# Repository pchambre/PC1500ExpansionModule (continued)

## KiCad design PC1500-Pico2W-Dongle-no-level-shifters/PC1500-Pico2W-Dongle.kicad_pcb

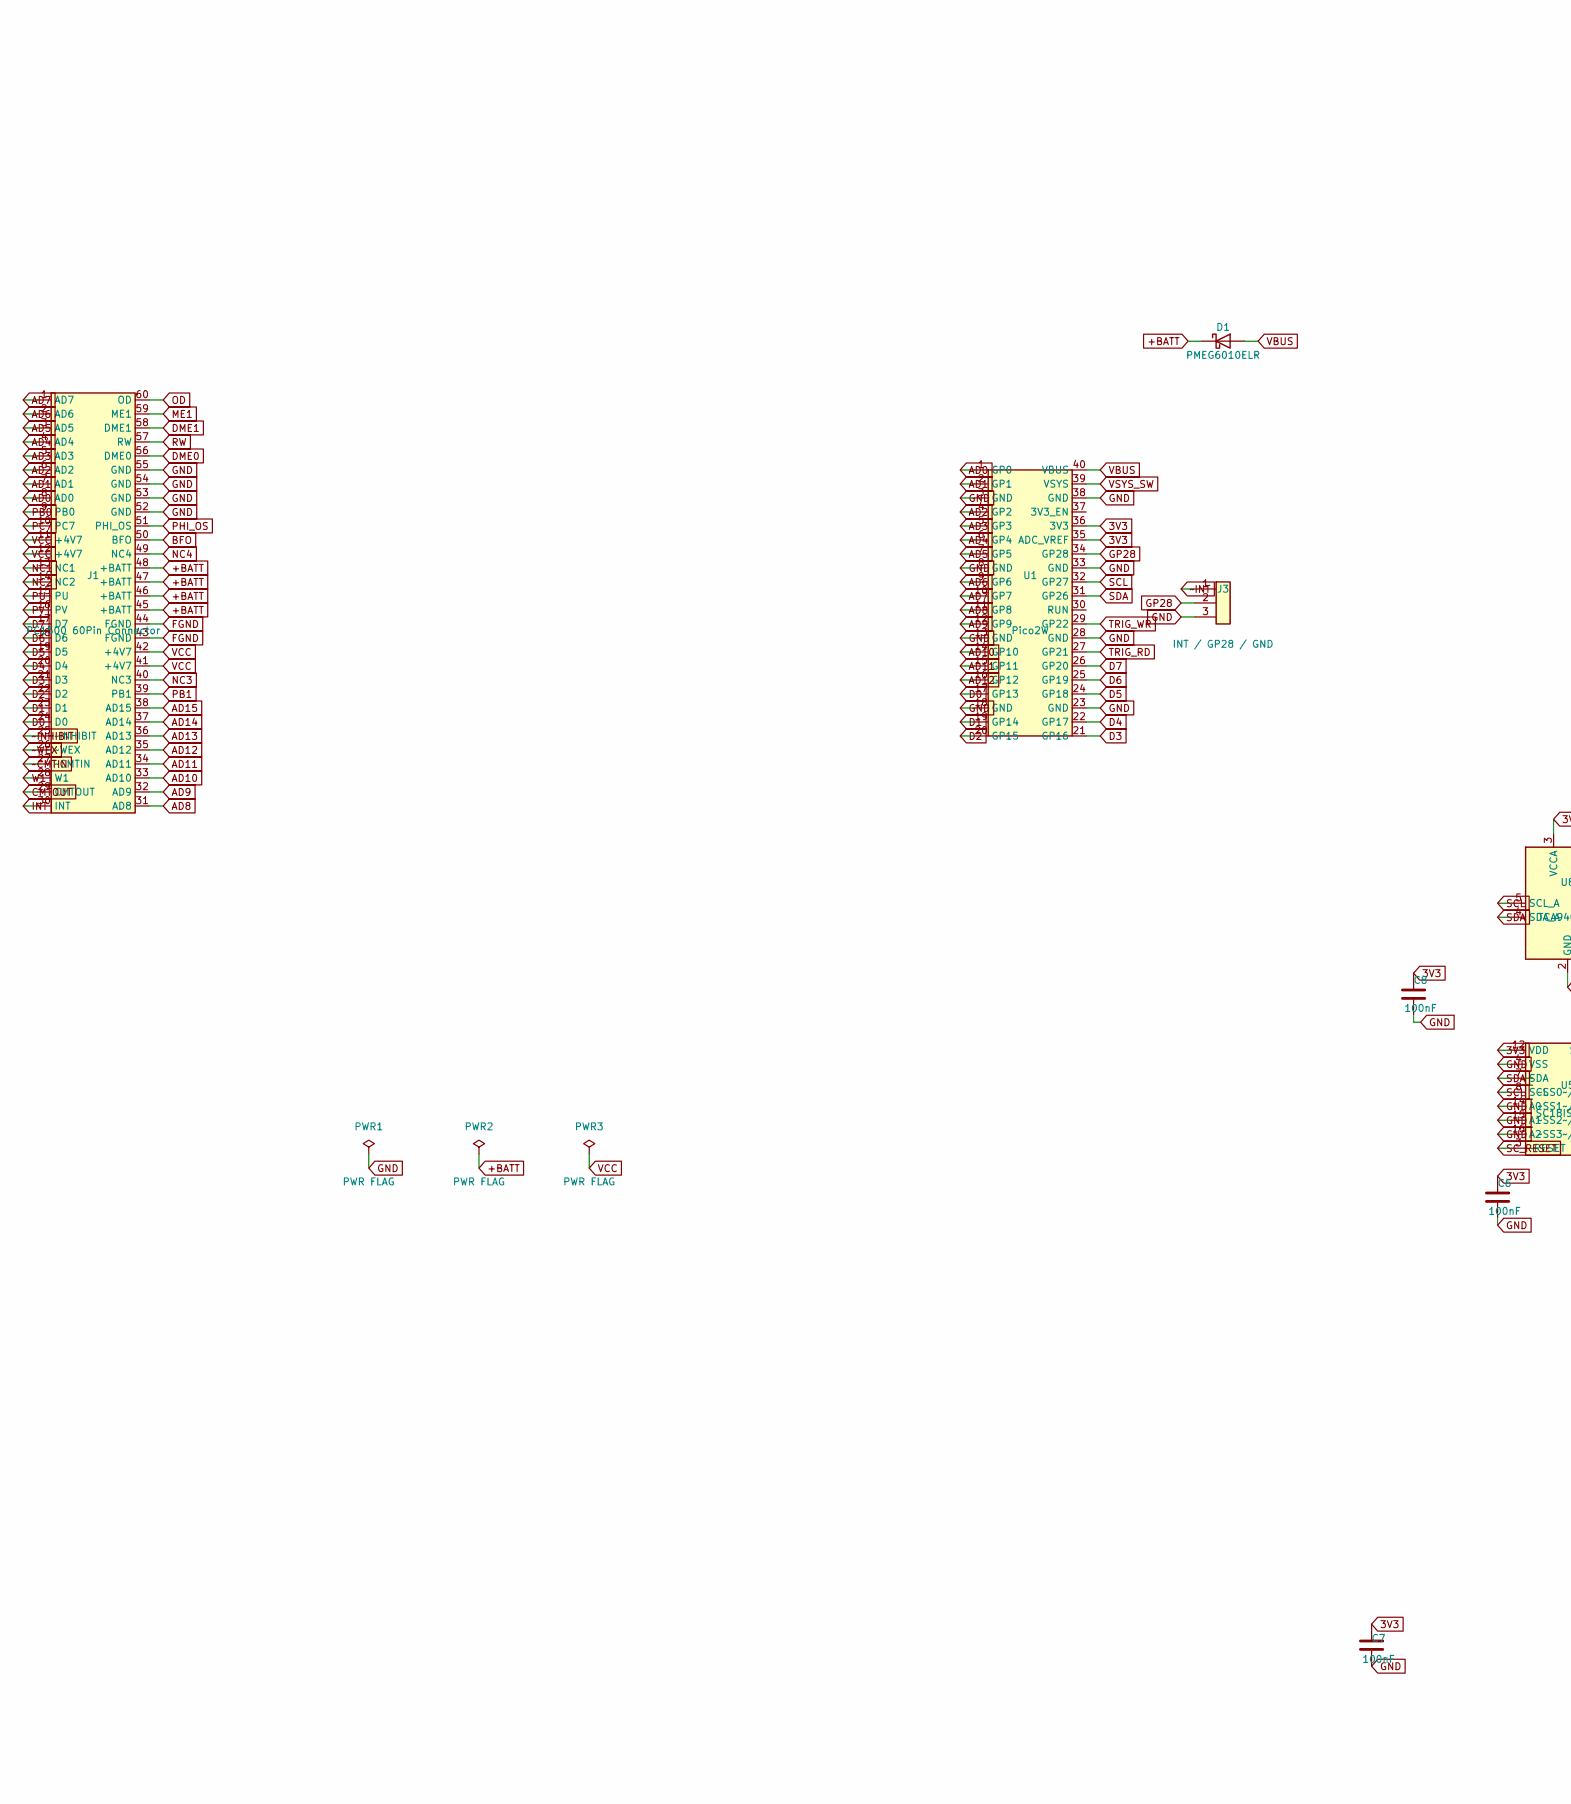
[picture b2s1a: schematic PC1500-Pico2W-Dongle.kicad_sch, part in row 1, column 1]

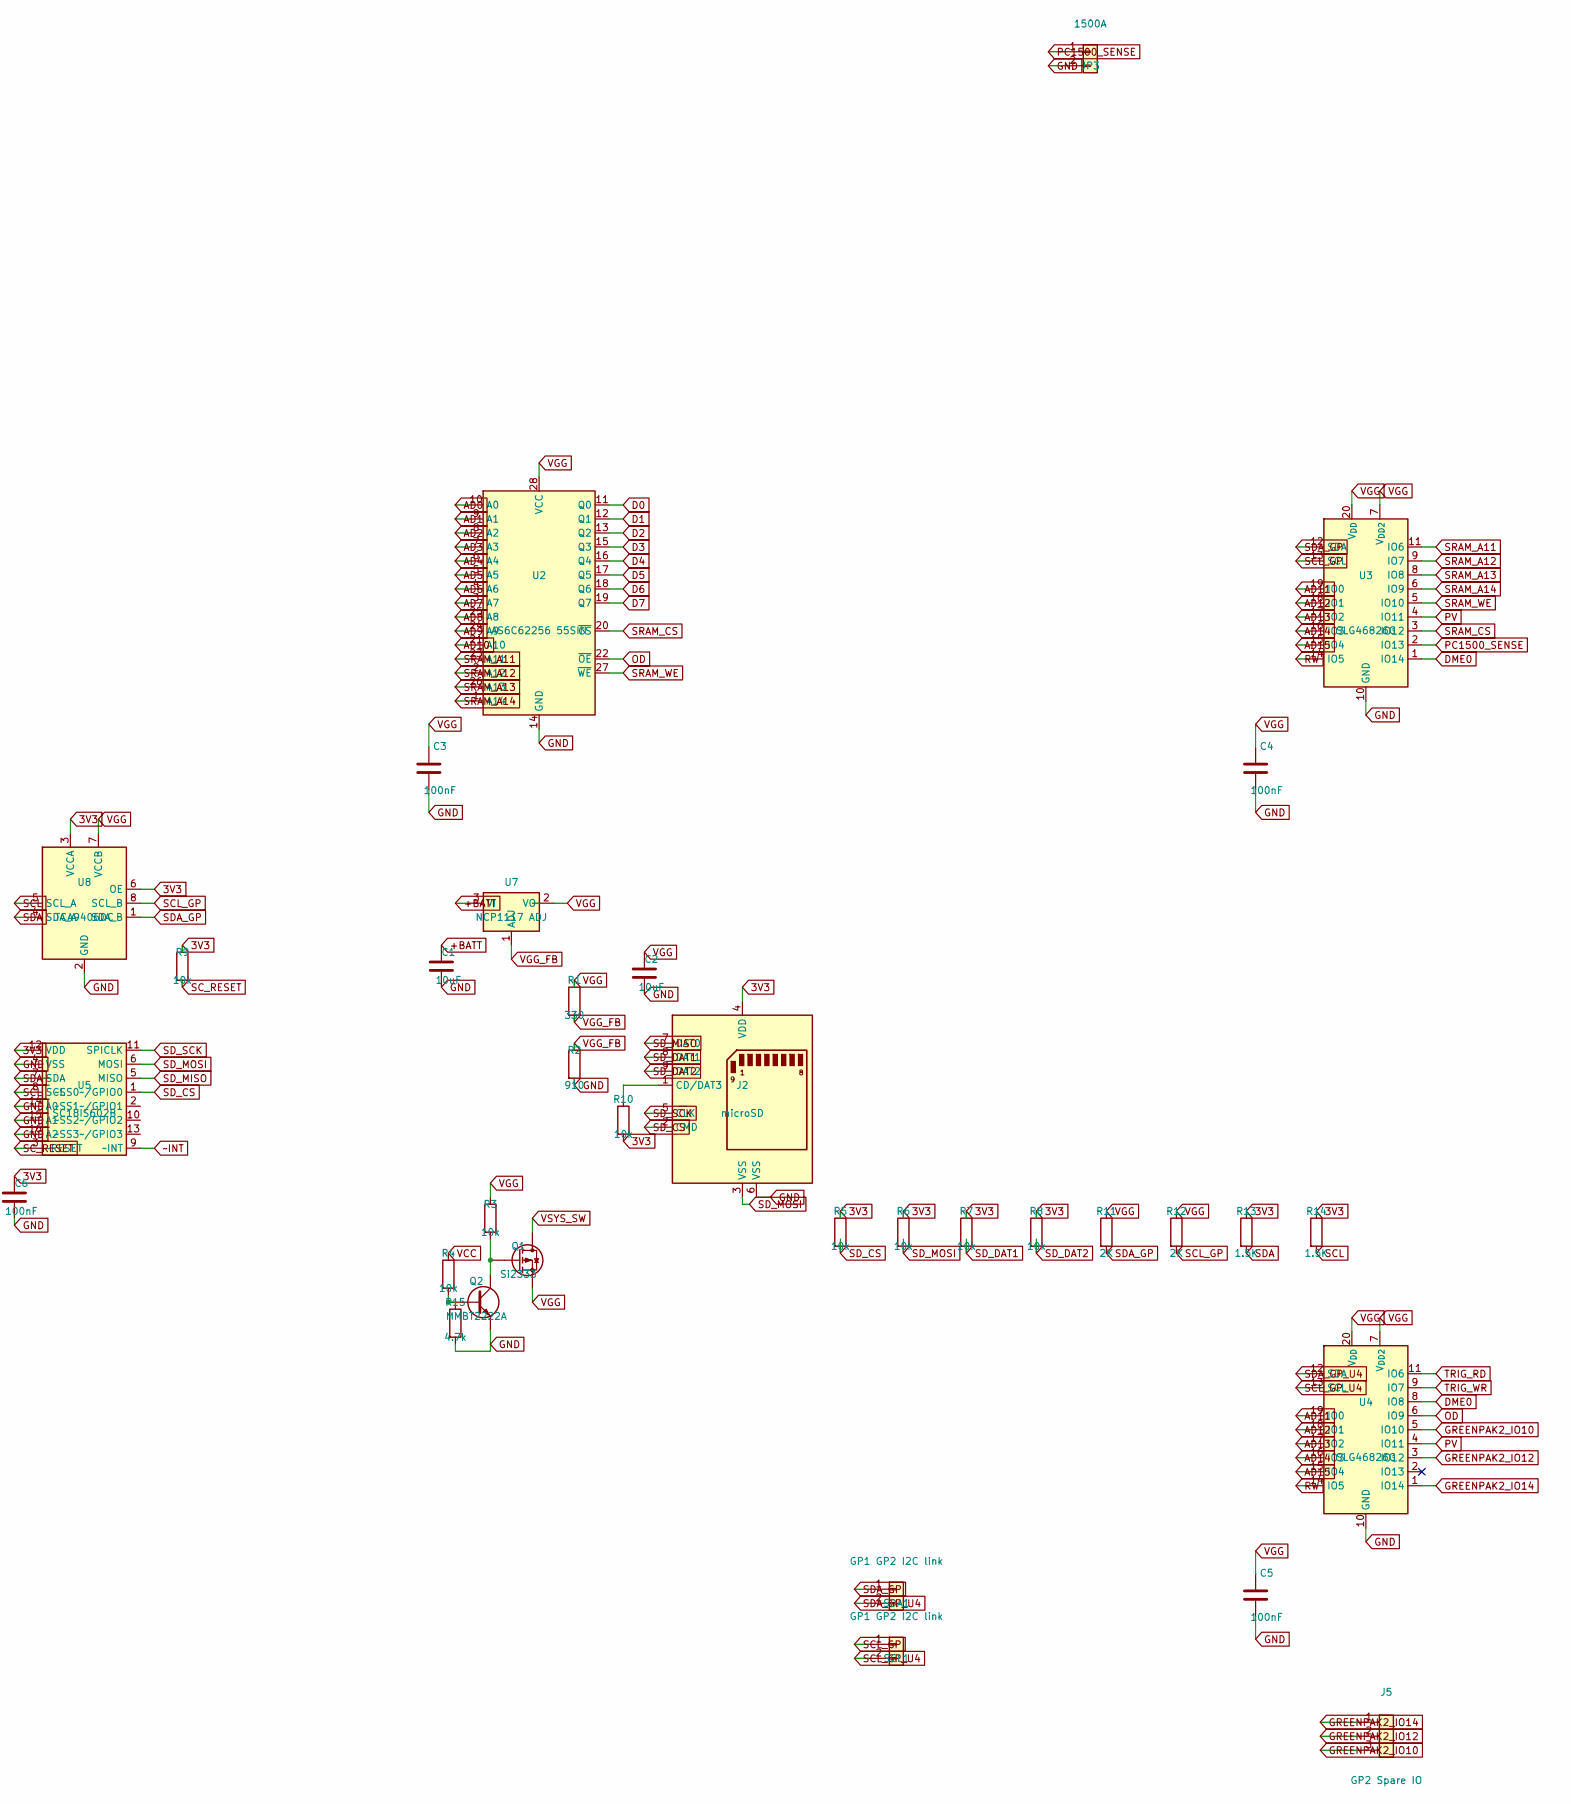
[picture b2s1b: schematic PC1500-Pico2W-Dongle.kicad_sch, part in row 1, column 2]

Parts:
C1, C2: 10uF; C_0603_1608Metric
C3, C4, C5, C6, C7, C8: 100nF; C_0603_1608Metric
D1: PMEG6010ELR; D_SOD-123F
J1: PC1500 60Pin Connector; HIF6A-60PA-1.27DS
J2: microSD; microSD_HC_Molex_104031-0811
J3: INT / GP28 / GND; PinHeader_1x03_P2.54mm_Vertical
J5: GP2 Spare IO; PinHeader_1x03_P2.54mm_Vertical
JP3: 1500A; PinHeader_1x02_P2.54mm_Vertical
PWR1, PWR2, PWR3: PWR FLAG
Q1: Si2333; SOT-23
Q2: MMBT2222A; SOT-23
R1: 330; R_0603_1608Metric
R2: 910; R_0603_1608Metric
R3, R4, R5, R6, R7, R8, R9, R10: 10k; R_0201_0603Metric
R11, R12: 2K; R_0201_0603Metric
R13, R14: 1.5K; R_0201_0603Metric
R15: 4.7k; R_0201_0603Metric
SCL1: GP1 GP2 I2C link; PinHeader_1x02_P2.54mm_Vertical
SDA1: GP1 GP2 I2C link; PinHeader_1x02_P2.54mm_Vertical
U1: Pico2W; Pico2W-Socket
U2: AS6C62256 55SIN; SOP-28_8.4x18.16mm_P1.27mm
U3, U4: SLG46826G; TSSOP-20_4.4x6.5mm_P0.65mm
U5: SC18IS602B; TSSOP-16_4.4x5mm_P0.65mm
U7: NCP1117 ADJ; SOT-223-3_TabPin2
U8: TCA9406DC; VSSOP-8_3x3mm_P0.65mm

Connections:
3V3: C6.1, C7.1, C8.1, J2.4 (VDD), R5.1, R6.1, R7.1, R8.1, R9.1, R10.2, R13.1, R14.1, U1.35 (ADC_VREF), U1.36 (3V3), U5.12 (VDD), U8.3 (VCCA), U8.6 (OE)
+BATT: C1.1, D1.1 (K), J1.45 (+BATT), J1.46 (+BATT), J1.47 (+BATT), J1.48 (+BATT), PWR2.1, U7.3 (VI)
AD0: J1.8 (AD0), U1.1 (GP0), U2.10 (A0)
AD1: J1.7 (AD1), U1.2 (GP1), U2.9 (A1)
AD2: J1.6 (AD2), U1.4 (GP2), U2.8 (A2)
AD3: J1.5 (AD3), U1.5 (GP3), U2.7 (A3)
AD4: J1.4 (AD4), U1.6 (GP4), U2.6 (A4)
AD5: J1.3 (AD5), U1.7 (GP5), U2.5 (A5)
AD6: J1.2 (AD6), U1.9 (GP6), U2.4 (A6)
AD7: J1.1 (AD7), U1.10 (GP7), U2.3 (A7)
AD8: J1.31 (AD8), U1.11 (GP8), U2.25 (A8)
AD9: J1.32 (AD9), U1.12 (GP9), U2.24 (A9)
AD10: J1.33 (AD10), U1.14 (GP10), U2.21 (A10)
AD11: J1.34 (AD11), U1.15 (GP11), U3.19 (IO0), U4.19 (IO0)
AD12: J1.35 (AD12), U1.16 (GP12), U3.18 (IO1), U4.18 (IO1)
AD13: J1.36 (AD13), U3.17 (IO2), U4.17 (IO2)
AD14: J1.37 (AD14), U3.16 (IO3), U4.16 (IO3)
AD15: J1.38 (AD15), U3.15 (IO4), U4.15 (IO4)
BFO: J1.50 (BFO)
CMTOUT: J1.29 (CMTOUT)
D0: J1.24 (D0), U1.17 (GP13), U2.11 (Q0)
D1: J1.23 (D1), U1.19 (GP14), U2.12 (Q1)
D2: J1.22 (D2), U1.20 (GP15), U2.13 (Q2)
D3: J1.21 (D3), U1.21 (GP16), U2.15 (Q3)
D4: J1.20 (D4), U1.22 (GP17), U2.16 (Q4)
D5: J1.19 (D5), U1.24 (GP18), U2.17 (Q5)
D6: J1.18 (D6), U1.25 (GP19), U2.18 (Q6)
D7: J1.17 (D7), U1.26 (GP20), U2.19 (Q7)
DME0: J1.56 (DME0), U3.1 (IO14), U4.8 (IO8)
DME1: J1.58 (DME1)
FGND: J1.43 (FGND), J1.44 (FGND)
GND: C1.2, C2.2, C3.2, C4.2, C5.2, C6.2, C7.2, C8.2, J1.52 (GND), J1.53 (GND), J1.54 (GND), J1.55 (GND), J2.6 (VSS), J3.3, JP3.2, PWR1.1, Q2.2 (E), R2.2, R15.2, U1.3 (GND), U1.8 (GND), U1.13 (GND), U1.18 (GND), U1.23 (GND), U1.28 (GND), U1.33 (GND), U1.38 (GND), U2.14 (GND), U3.10 (GND), U4.10 (GND), U5.4 (VSS), U5.14 (A0), U5.15 (A1), U5.16 (A2), U8.2 (GND)
GP28: J3.2, U1.34 (GP28)
GREENPAK2_IO10: J5.3, U4.5 (IO10)
GREENPAK2_IO12: J5.2, U4.3 (IO12)
GREENPAK2_IO14: J5.1, U4.1 (IO14)
INT: J1.30 (INT)
ME1: J1.59 (ME1)
NC1: J1.13 (NC1)
NC2: J1.14 (NC2)
NC3: J1.40 (NC3)
NC4: J1.49 (NC4)
unnamed: J2.1 (CD/DAT3), R10.1
unnamed: Q1.1 (G), Q2.3 (C), R3.2
unnamed: Q2.1 (B), R4.2, R15.1
OD: J1.60 (OD), U2.22 (~OE), U4.6 (IO9)
PB0: J1.9 (PB0)
PB1: J1.39 (PB1)
PC7: J1.10 (PC7)
PC1500_SENSE: JP3.1, U3.2 (IO13)
PHI_OS: J1.51 (PHI_OS)
PU: J1.15 (PU)
PV: J1.16 (PV), U3.4 (IO11), U4.4 (IO11)
RW: J1.57 (RW), U3.14 (IO5), U4.14 (IO5)
SCL: R14.2, U1.32 (GP27), U5.8 (SCL), U8.5 (SCL_A)
SCL_GP: R12.2, SCL1.1, U3.13 (SCL), U8.8 (SCL_B)
SCL_GP_U4: SCL1.2, U4.13 (SCL)
SC_RESET: R9.2, U5.3 (~RESET)
SDA: R13.2, U1.31 (GP26), U5.7 (SDA), U8.4 (SDA_A)
SDA_GP: R11.2, SDA1.1, U3.12 (SDA), U8.1 (SDA_B)
SDA_GP_U4: SDA1.2, U4.12 (SDA)
SD_CS: J2.2 (CMD), R5.2, U5.1 (~SS0~/GPIO0)
SD_DAT1: J2.8 (DAT1), R7.2
SD_DAT2: J2.9 (DAT2), R8.2
SD_MISO: J2.7 (DAT0), U5.5 (MISO)
SD_MOSI: J2.3 (VSS), R6.2, U5.6 (MOSI)
SD_SCK: J2.5 (CLK), U5.11 (SPICLK)
SRAM_A11: U2.23 (A11), U3.11 (IO6)
SRAM_A12: U2.2 (A12), U3.9 (IO7)
SRAM_A13: U2.26 (A13), U3.8 (IO8)
SRAM_A14: U2.1 (A14), U3.6 (IO9)
SRAM_CS: U2.20 (~CS), U3.3 (IO12)
SRAM_WE: U2.27 (~WE), U3.5 (IO10)
TRIG_RD: U1.27 (GP21), U4.11 (IO6)
TRIG_WR: U1.29 (GP22), U4.9 (IO7)
VBUS: D1.2 (A), U1.40 (VBUS)
VCC: J1.11 (+4V7), J1.12 (+4V7), J1.41 (+4V7), J1.42 (+4V7), PWR3.1, R4.1
VGG: C2.1, C3.1, C4.1, C5.1, Q1.2 (S), R1.1, R3.1, R11.1, R12.1, U2.28 (VCC), U3.7 (V_{DD2}), U3.20 (V_{DD}), U4.7 (V_{DD2}), U4.20 (V_{DD}), U7.2 (VO), U8.7 (VCCB)
VGG_FB: R1.2, R2.1, U7.1 (ADJ)
VSYS_SW: Q1.3 (D), U1.39 (VSYS)
W1: J1.28 (W1)
~CMTIN: J1.27 (~CMTIN)
~INHIBIT: J1.25 (~INHIBIT)
~INT: J3.1, U5.9 (~INT)
~WEX: J1.26 (~WEX)

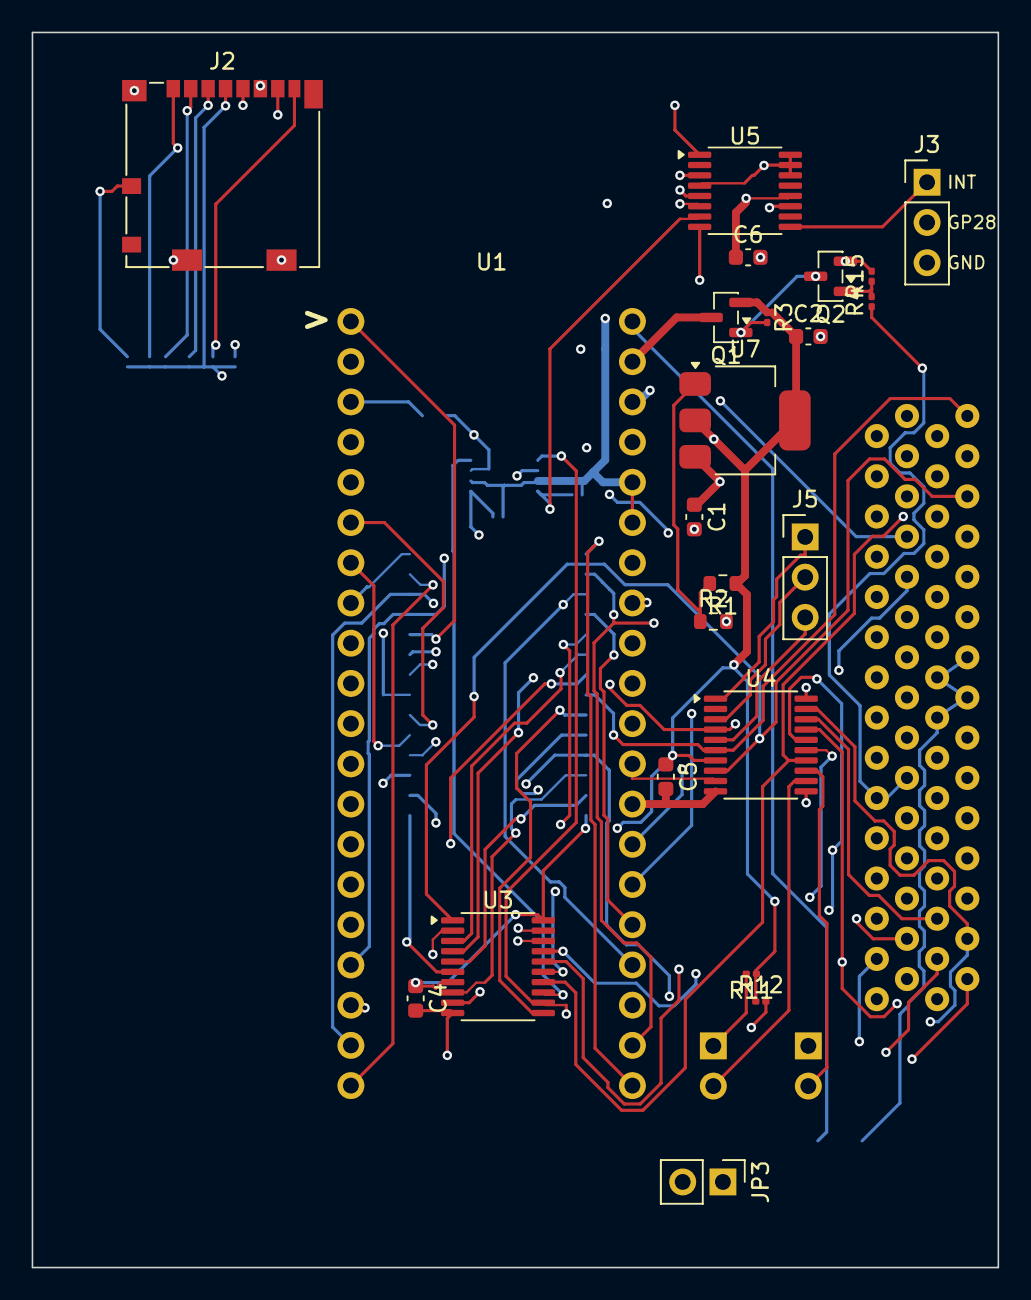
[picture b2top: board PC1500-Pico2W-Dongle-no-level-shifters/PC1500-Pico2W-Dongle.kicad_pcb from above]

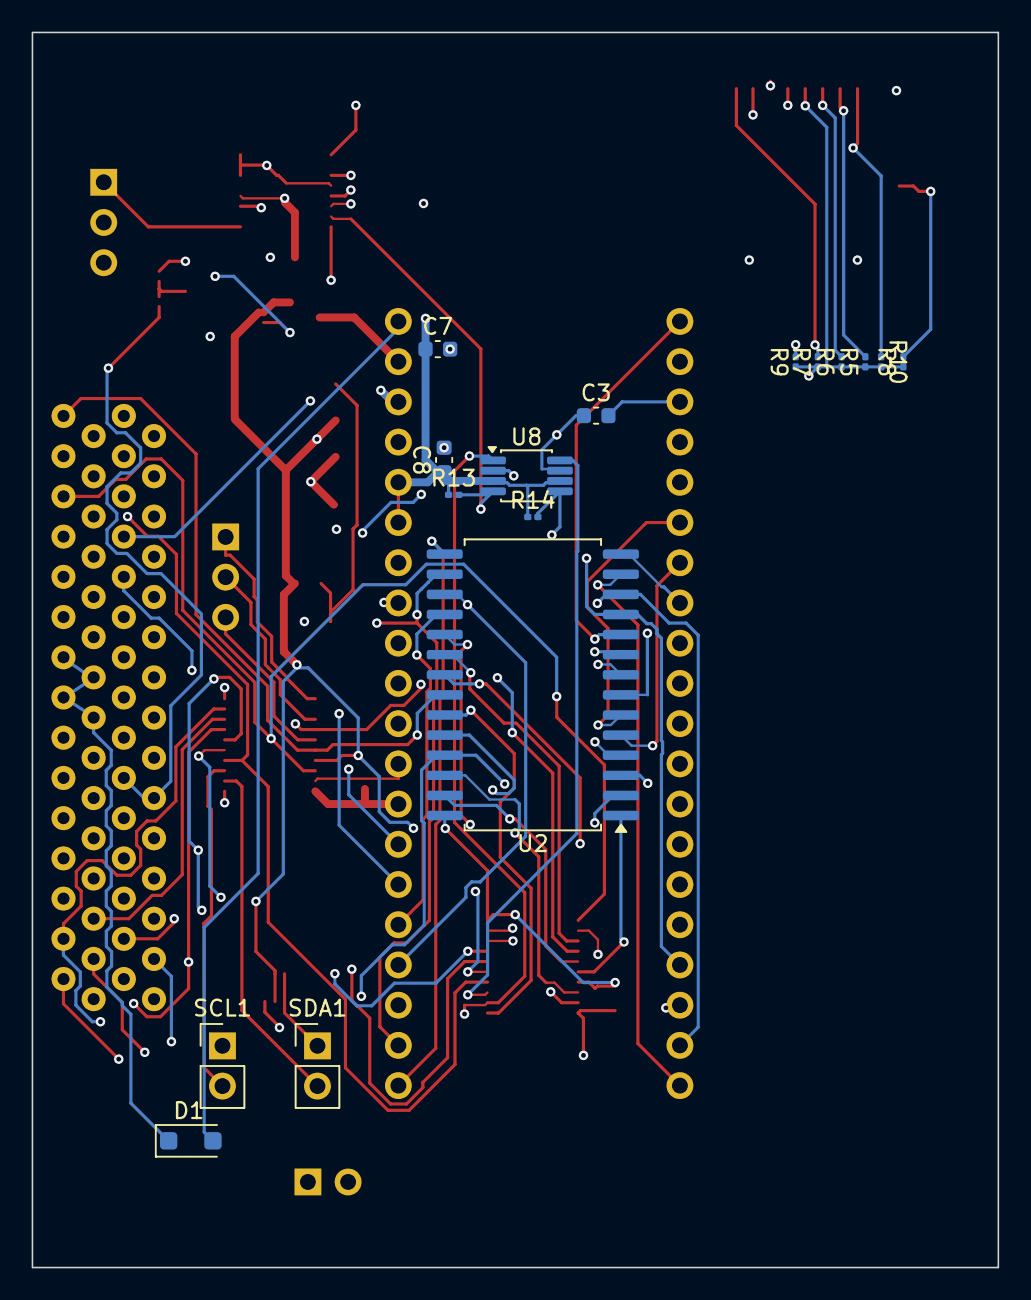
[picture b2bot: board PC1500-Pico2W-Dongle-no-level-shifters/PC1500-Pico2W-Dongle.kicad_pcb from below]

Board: 4 copper layers, 61.0 x 78.0 mm, 40 parts (16 on the bottom side), 67 nets.

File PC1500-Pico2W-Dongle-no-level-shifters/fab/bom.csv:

"Refs","Value","Footprint","Qty","DNP"
"C1,C2","10uF","Capacitor SMD:C 0603 1608Metric","2",""
"C3,C4,C5,C6,C7,C8","100nF","Capacitor SMD:C 0603 1608Metric","6",""
"D1","PMEG6010ELR","Diode SMD:D SOD 123F","1",""
"J1","PC1500 60Pin Connector","Pico2W Dongle Footprints:HIF6A 60PA 1.27DS","1",""
"J2","microSD","Connector Card:microSD HC Molex 104031 0811","1",""
"J3","INT / GP28 / GND","Connector PinHeader 2.54mm:PinHeader 1x03 P2.54mm Vertical","1",""
"J5","GP2 Spare IO","Connector PinHeader 2.54mm:PinHeader 1x03 P2.54mm Vertical","1",""
"JP3","1500A","Connector PinHeader 2.54mm:PinHeader 1x02 P2.54mm Vertical","1",""
"Q1","Si2333","Package TO SOT SMD:SOT 23","1",""
"Q2","MMBT2222A","Package TO SOT SMD:SOT 23","1",""
"R1","330Ω","Resistor SMD:R 0201 0603Metric","1",""
"R2","910Ω","Resistor SMD:R 0201 0603Metric","1",""
"R3,R4,R5,R6,R7,R8,R9,R10","10kΩ","Resistor SMD:R 0201 0603Metric","8",""
"R11,R12","2KΩ","Resistor SMD:R 0201 0603Metric","2",""
"R13,R14","1.5KΩ","Resistor SMD:R 0201 0603Metric","2",""
"SCL1,SDA1","GP1 GP2 I2C link","Connector PinHeader 2.54mm:PinHeader 1x02 P2.54mm Vertical","2",""
"U1","Pico2W","Pico2W Dongle Footprints:Pico2W Socket","1",""
"U2","AS6C62256 55SIN","Package SO:SOP 28 8.4x18.16mm P1.27mm","1",""
"U3,U4","SLG46826G","Package SO:TSSOP 20 4.4x6.5mm P0.65mm","2",""
"U5","SC18IS602B","Package SO:TSSOP 16 4.4x5mm P0.65mm","1",""
"U7","NCP1117 ADJ","Package TO SOT SMD:SOT 223 3 TabPin2","1",""
"U8","TCA9406DC","Package SO:VSSOP 8 3x3mm P0.65mm","1",""

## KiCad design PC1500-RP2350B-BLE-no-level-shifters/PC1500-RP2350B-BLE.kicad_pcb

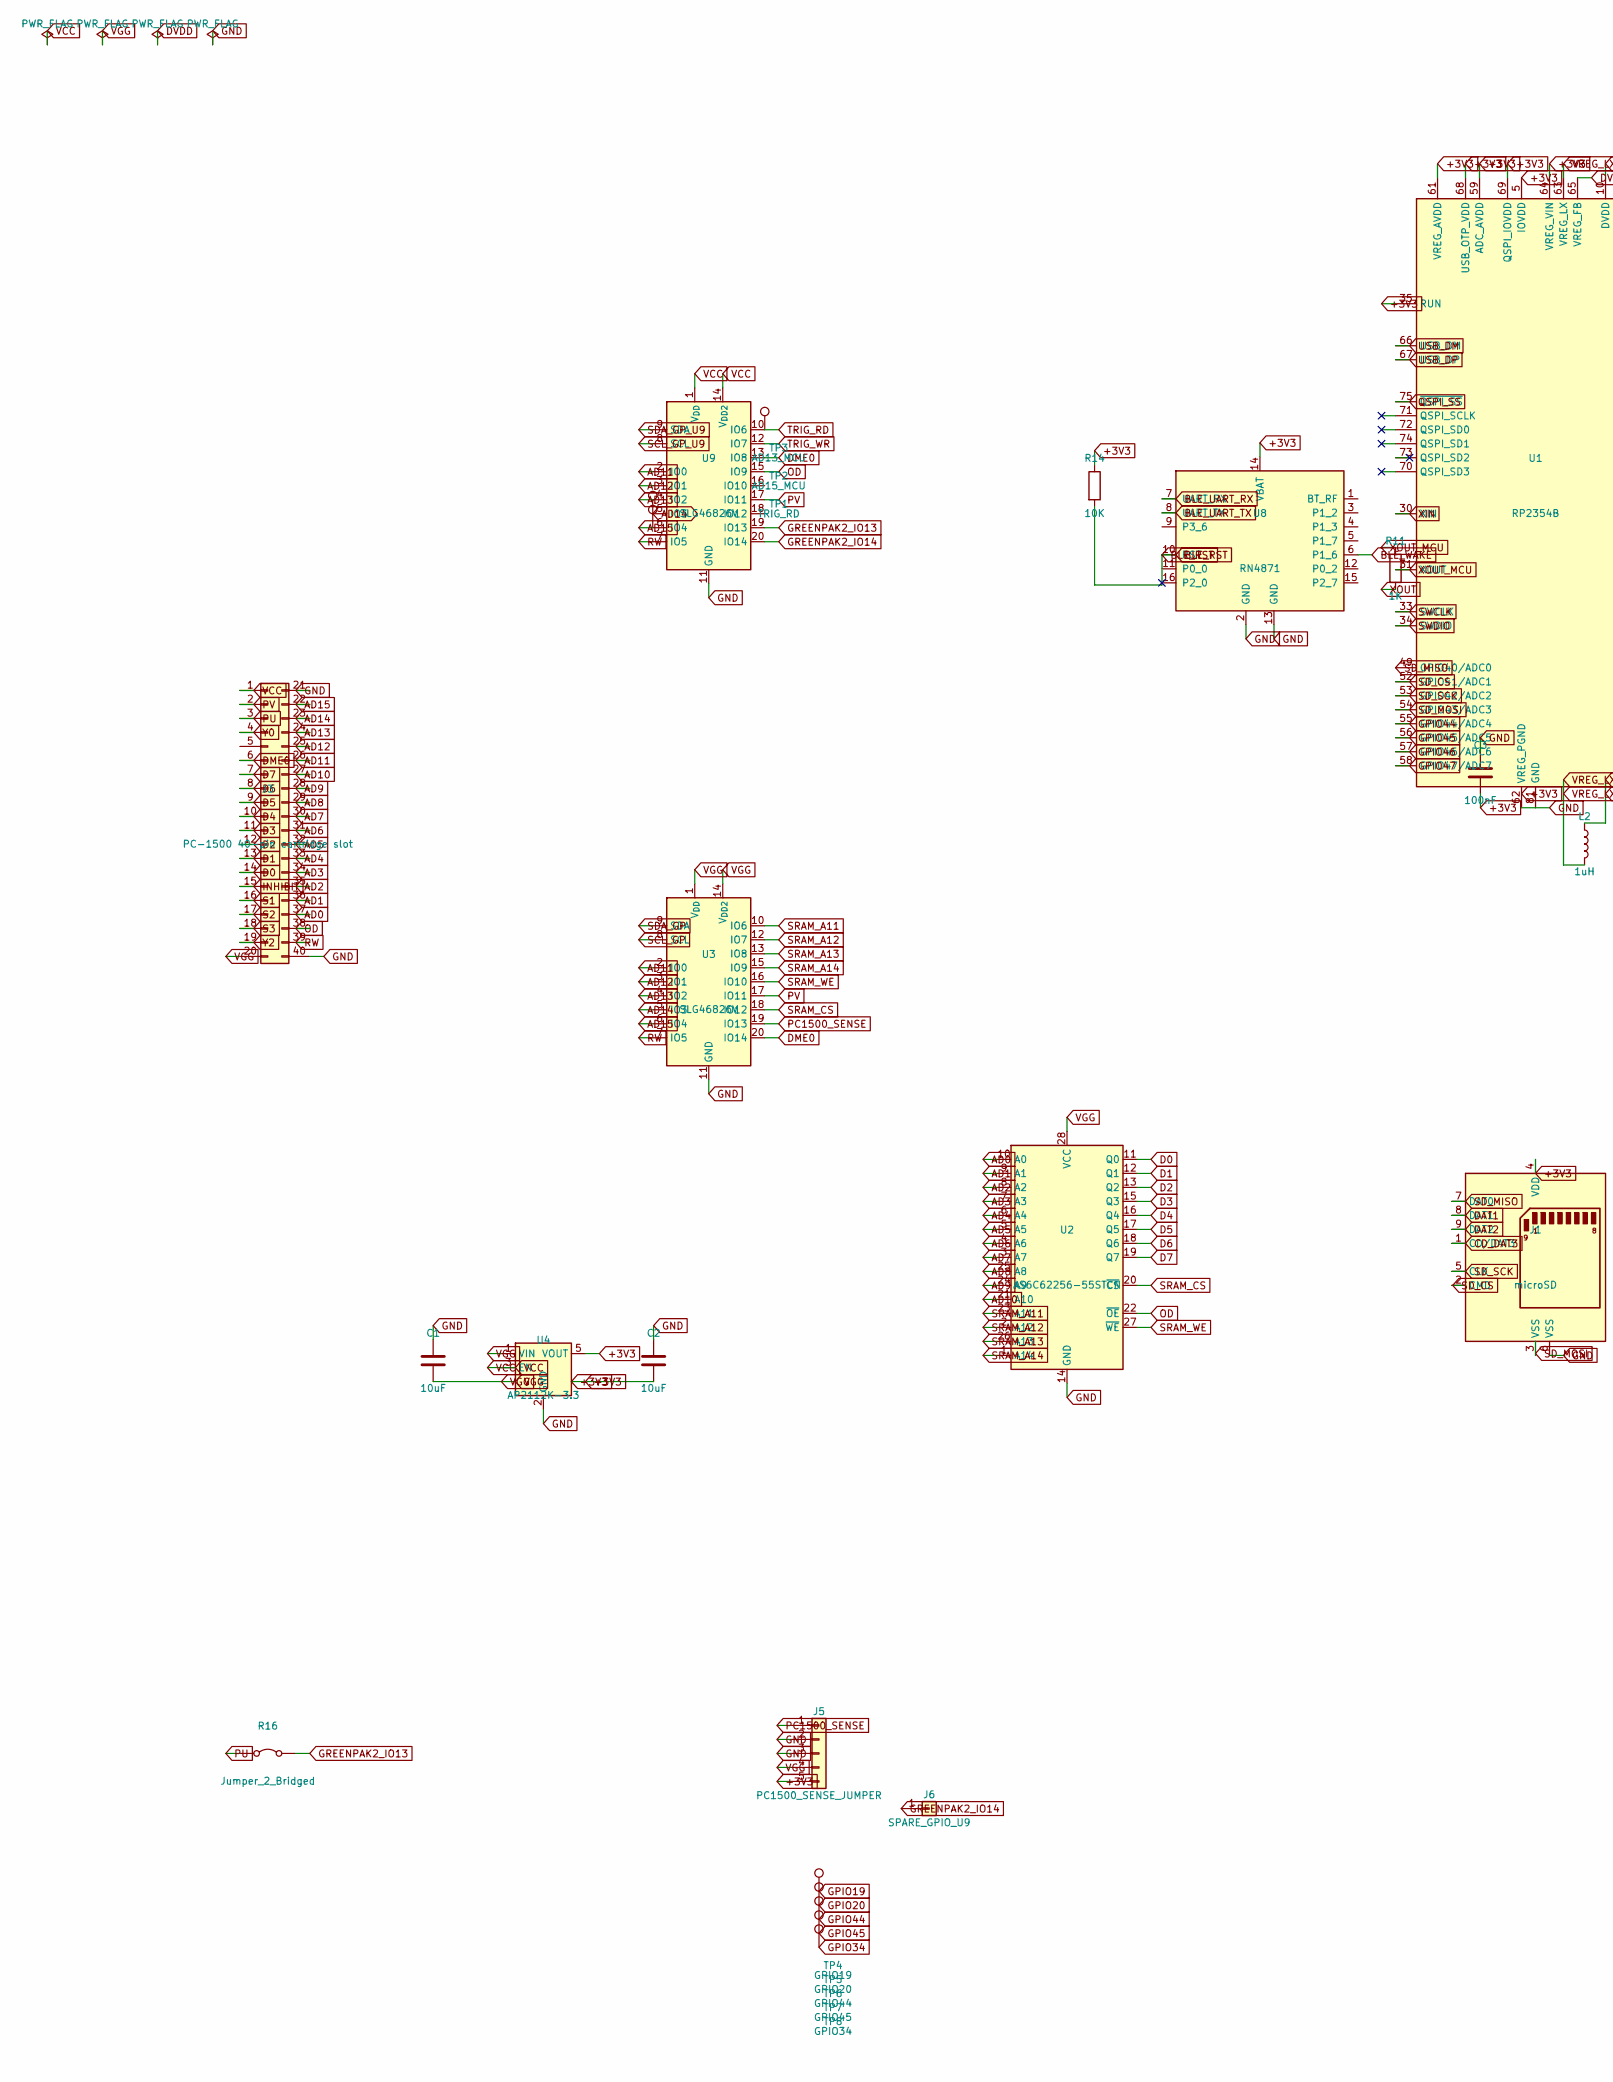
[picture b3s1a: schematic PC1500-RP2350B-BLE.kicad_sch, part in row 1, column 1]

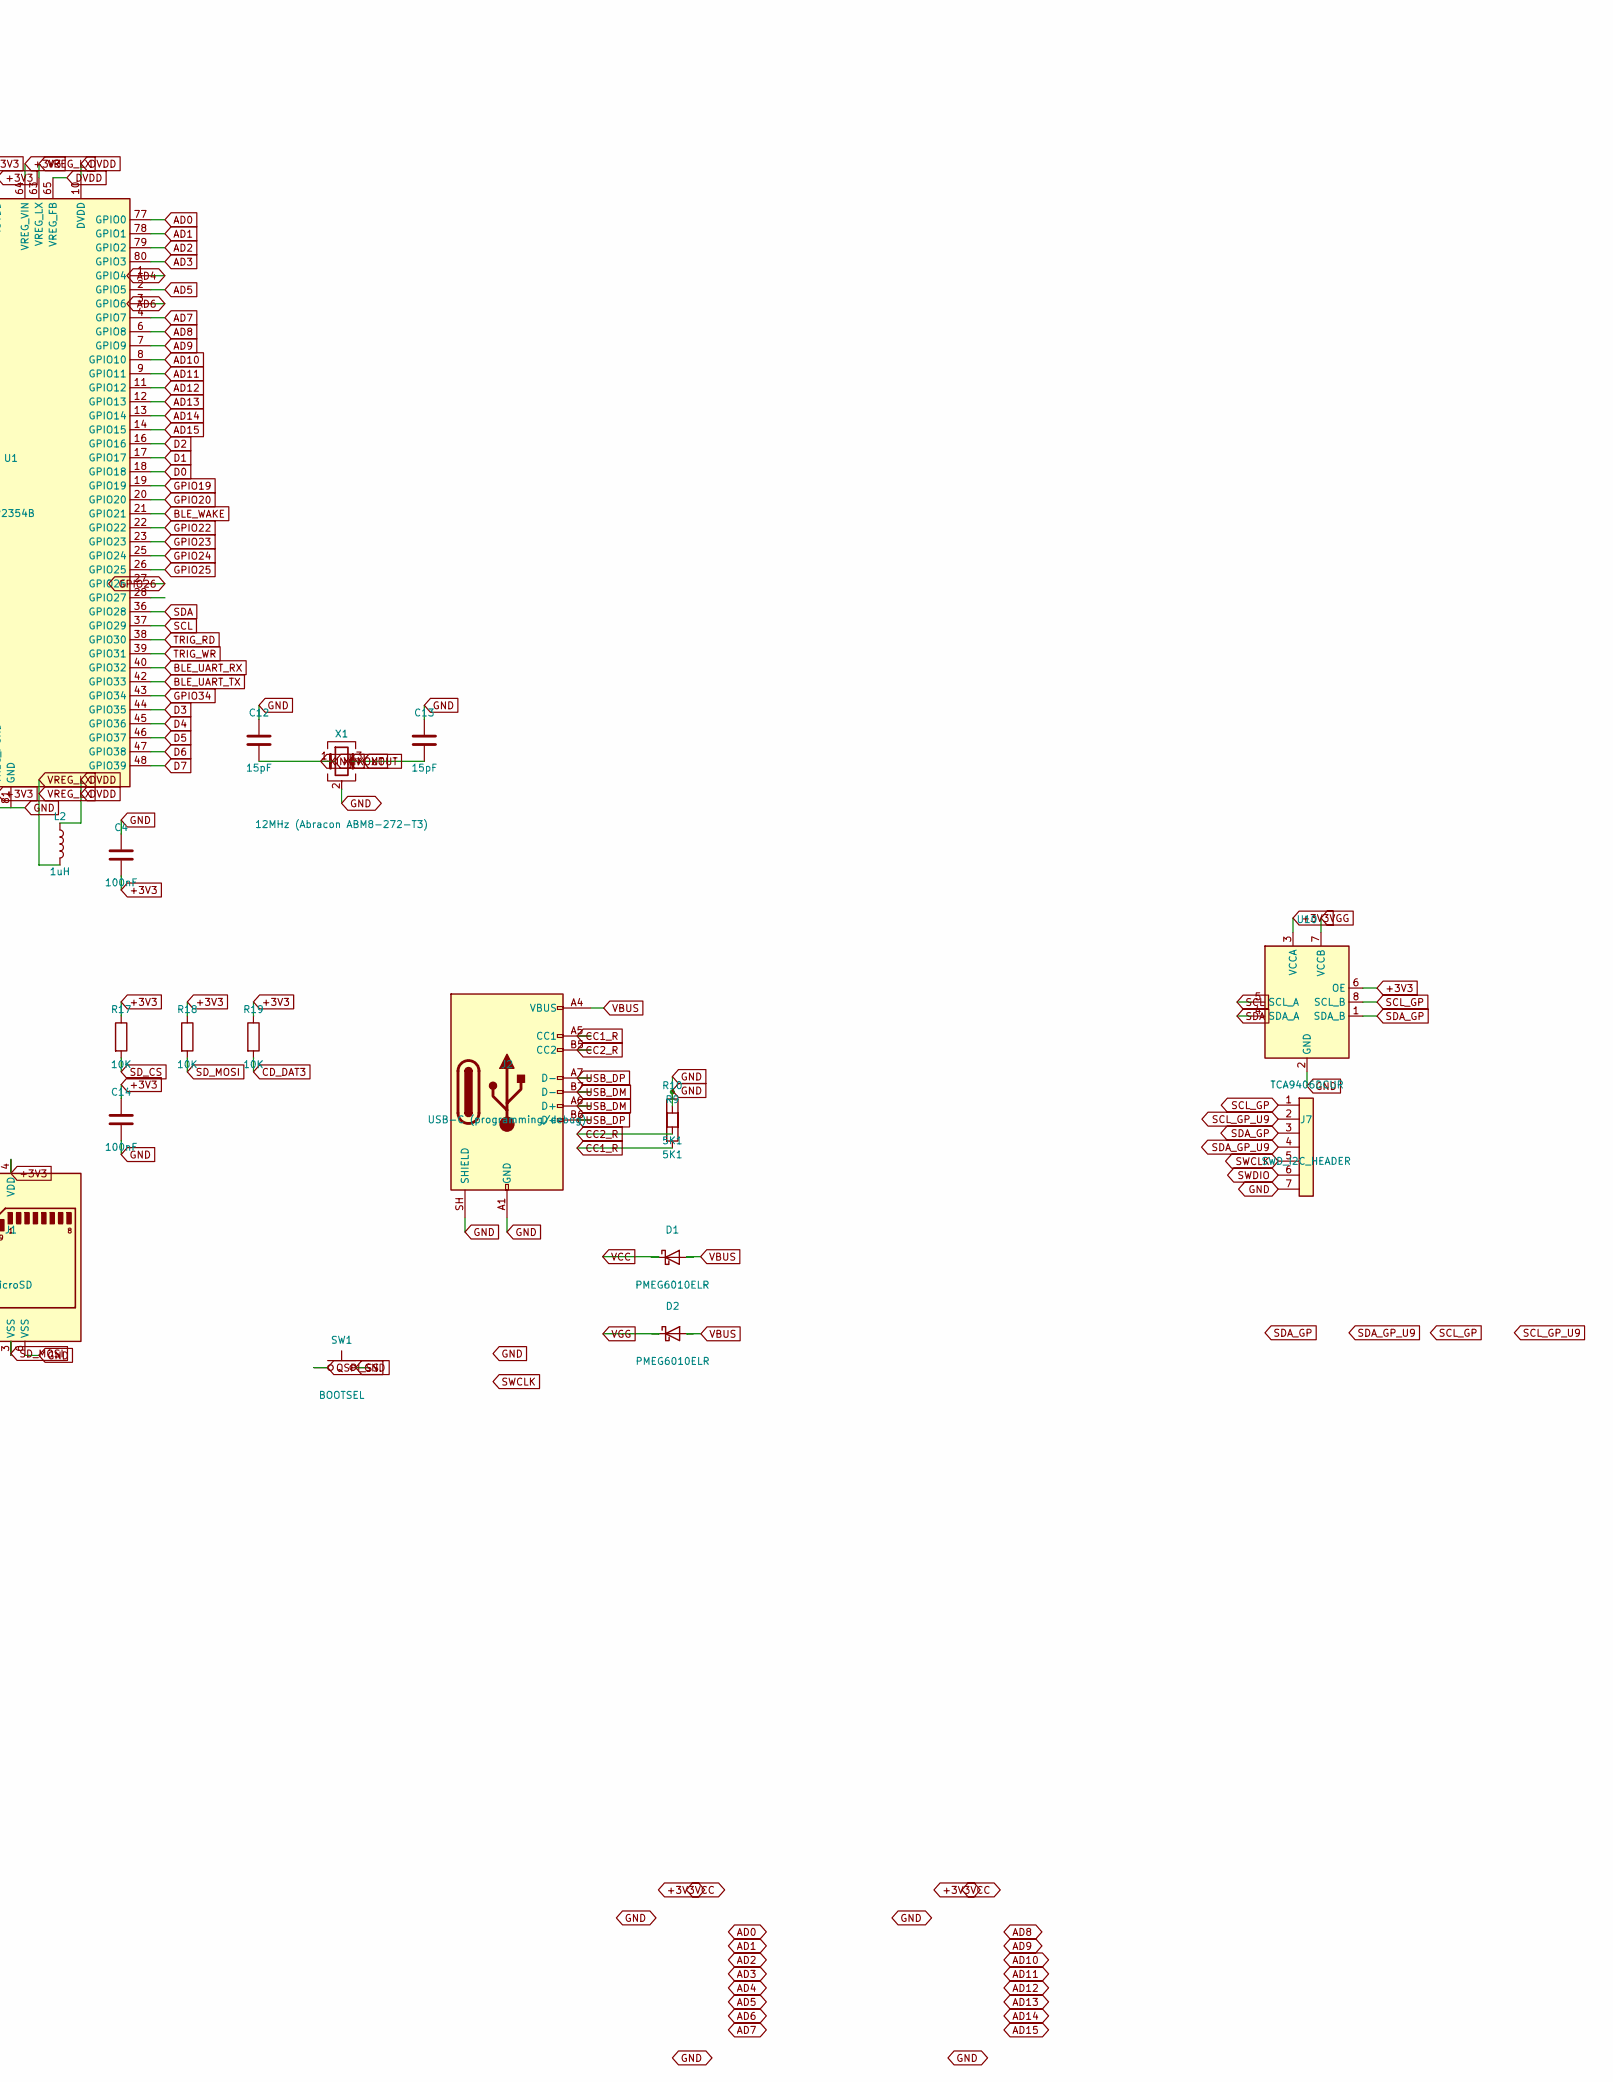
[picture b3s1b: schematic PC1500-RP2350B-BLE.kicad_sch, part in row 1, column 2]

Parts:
C1, C2: 10uF; C_0805_2012Metric
C3, C4, C14: 100nF; C_0402_1005Metric
C12, C13: 15pF; C_0603_1608Metric
D1, D2: PMEG6010ELR; D_SOD-123F
FLG1, FLG2, FLG3, FLG4: PWR_FLAG
J1: microSD; microSD_HC_Molex_104031-0811
J2: USB-C (programming/debug); USB_C_Receptacle_HRO_TYPE-C-31-M-12
J3: PC-1500 40-pin cartridge slot; SHARP-PC-CARTRIDGE
J5: PC1500_SENSE_JUMPER; PinHeader_1x05_P2.54mm_Vertical
J6: SPARE_GPIO_U9; PinHeader_1x01_P2.54mm_Vertical
J7: SWD_I2C_HEADER; PinHeader_1x07_P2.54mm_Vertical
L2: 1uH; L_0805_2012Metric
R9, R10: 5K1; R_0201_0603Metric
R11: 1K; R_0201_0603Metric
R14, R17, R18, R19: 10K; R_0201_0603Metric
R16: Jumper_2_Bridged; SolderJumper-2_P1.3mm_Bridged_RoundedPad1.0x1.5mm
SW1: BOOTSEL; SW_SPST_TL3342
TP1: TRIG_RD; TestPoint_Pad_1.0x1.0mm
TP2: AD15_MCU; TestPoint_Pad_1.0x1.0mm
TP3: AD13_MCU; TestPoint_Pad_1.0x1.0mm
TP4: GPIO19; TestPoint_Pad_1.0x1.0mm
TP5: GPIO20; TestPoint_Pad_1.0x1.0mm
TP6: GPIO44; TestPoint_Pad_1.0x1.0mm
TP7: GPIO45; TestPoint_Pad_1.0x1.0mm
TP8: GPIO34; TestPoint_Pad_1.0x1.0mm
U1: RP2354B; QFN-80-1EP_10x10mm_P0.4mm_EP3.4x3.4mm
U2: AS6C62256-55STCN; AS6C62256_STSOP-28_11.8x8mm_P0.55mm
U3, U9: SLG46826V; Renesas_UQFN-20_2x3mm_P0.4mm_LayoutBorder4x6y
U4: AP2112K-3.3; SOT-23-5
U8: RN4871; Microchip_RN4871
U10: TCA9406DCUR; VSSOP-8_2.3x2mm_P0.5mm
X1: 12MHz (Abracon ABM8-272-T3); Crystal_SMD_3225-4Pin_3.2x2.5mm

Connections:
+3V3: C2.2, C3.2, C4.2, C14.1, J1.4 (VDD), J5.5, R14.1, R17.1, R18.1, R19.1, U1.5 (IOVDD), U1.15 (IOVDD), U1.24 (IOVDD), U1.29 (IOVDD), U1.35 (RUN), U1.41 (IOVDD), U1.50 (IOVDD), U1.59 (ADC_AVDD), U1.60 (IOVDD), U1.61 (VREG_AVDD), U1.64 (VREG_VIN), U1.68 (USB_OTP_VDD), U1.69 (QSPI_IOVDD), U1.76 (IOVDD), U4.5 (VOUT), U8.14 (VBAT), U10.3 (VCCA), U10.6 (OE)
AD0: J3.37, U1.77 (GPIO0), U2.10 (A0)
AD1: J3.36, U1.78 (GPIO1), U2.9 (A1)
AD2: J3.35, U1.79 (GPIO2), U2.8 (A2)
AD3: J3.34, U1.80 (GPIO3), U2.7 (A3)
AD4: J3.33, U1.1 (GPIO4), U2.6 (A4)
AD5: J3.32, U1.2 (GPIO5), U2.5 (A5)
AD6: J3.31, U1.3 (GPIO6), U2.4 (A6)
AD7: J3.30, U1.4 (GPIO7), U2.3 (A7)
AD8: J3.29, U1.6 (GPIO8), U2.25 (A8)
AD9: J3.28, U1.7 (GPIO9), U2.24 (A9)
AD10: J3.27, U1.8 (GPIO10), U2.21 (A10)
AD11: J3.26, U1.9 (GPIO11), U3.2 (IO0), U9.2 (IO0)
AD12: J3.25, U1.11 (GPIO12), U3.3 (IO1), U9.3 (IO1)
AD13: J3.24, U1.12 (GPIO13), U3.4 (IO2), U9.4 (IO2)
AD14: J3.23, TP2.1 (1_1), U1.13 (GPIO14), U3.5 (IO3), U9.5 (IO3)
AD15: J3.22, TP3.1 (1_1), U1.14 (GPIO15), U3.6 (IO4), U9.6 (IO4)
BLE_RST: R14.2, U8.10 (RST)
BLE_UART_RX: U1.40 (GPIO32), U8.7 (UART_RX)
BLE_UART_TX: U1.42 (GPIO33), U8.8 (UART_TX)
BLE_WAKE: U1.21 (GPIO21), U8.6 (P1_6)
CC1_R: J2.A5 (CC1), R9.2
CC2_R: J2.B5 (CC2), R10.2
CD_DAT3: J1.1 (CD/DAT3), R19.2
D0: J3.14, U1.18 (GPIO18), U2.11 (Q0)
D1: J3.13, U1.17 (GPIO17), U2.12 (Q1)
D2: J3.12, U1.16 (GPIO16), U2.13 (Q2)
D3: J3.11, U1.44 (GPIO35), U2.15 (Q3)
D4: J3.10, U1.45 (GPIO36), U2.16 (Q4)
D5: J3.9, U1.46 (GPIO37), U2.17 (Q5)
D6: J3.8, U1.47 (GPIO38), U2.18 (Q6)
D7: J3.7, U1.48 (GPIO39), U2.19 (Q7)
DAT1: J1.8 (DAT1)
DAT2: J1.9 (DAT2)
DME0: J3.6, U3.20 (IO14), U9.13 (IO8)
DVDD: FLG3.1, L2.1, U1.10 (DVDD), U1.32 (DVDD), U1.51 (DVDD), U1.65 (VREG_FB)
GND: C1.1, C2.1, C3.1, C4.1, C12.1, C13.1, C14.2, FLG4.1, J1.6 (VSS), J2.A1 (GND), J2.A12 (GND), J2.B1 (GND), J2.B12 (GND), J2.SH (SHIELD), J3.21, J3.40, J5.2, J5.3, J7.7, R9.1, R10.1, SW1.2, U1.62 (VREG_PGND), U1.81 (GND), U2.14 (GND), U3.11 (GND), U4.2 (GND), U8.2 (GND), U8.13 (GND), U9.11 (GND), U10.2 (GND), X1.2, X1.4 (G)
GPIO19: TP4.1 (1_1), U1.19 (GPIO19)
GPIO20: TP5.1 (1_1), U1.20 (GPIO20)
GPIO22: U1.22 (GPIO22)
GPIO23: U1.23 (GPIO23)
GPIO24: U1.25 (GPIO24)
GPIO25: U1.26 (GPIO25)
GPIO26: U1.27 (GPIO26)
GPIO34: TP8.1 (1_1), U1.43 (GPIO34)
GPIO44: TP6.1 (1_1), U1.55 (GPIO44/ADC4)
GPIO45: TP7.1 (1_1), U1.56 (GPIO45/ADC5)
GPIO46: U1.57 (GPIO46/ADC6)
GPIO47: U1.58 (GPIO47/ADC7)
GREENPAK2_IO13: R16.2 (B), U9.19 (IO13)
GREENPAK2_IO14: J6.1 (Pin_1_1), U9.20 (IO14)
INHIBIT: J3.15
OD: J3.38, U2.22 (~OE), U9.15 (IO9)
PC1500_SENSE: J5.1, U3.19 (IO13)
PU: J3.3, R16.1 (A)
PV: J3.2, U3.17 (IO11), U9.17 (IO11)
QSPI_SS: SW1.1, U1.75 (~QSPI_SS)
RW: J3.39, U3.7 (IO5), U9.7 (IO5)
S1: J3.16
S2: J3.17
S3: J3.18
SCL: U1.37 (GPIO29), U10.5 (SCL_A)
SCL_GP: J7.1, U3.8 (SCL), U10.8 (SCL_B)
SCL_GP_U9: J7.2, U9.8 (SCL)
SDA: U1.36 (GPIO28), U10.4 (SDA_A)
SDA_GP: J7.3, U3.9 (SDA), U10.1 (SDA_B)
SDA_GP_U9: J7.4, U9.9 (SDA)
SD_CS: J1.2 (CMD), R17.2, U1.52 (GPIO41/ADC1)
SD_MISO: J1.7 (DAT0), U1.49 (GPIO40/ADC0)
SD_MOSI: J1.3 (VSS), R18.2, U1.54 (GPIO43/ADC3)
SD_SCK: J1.5 (CLK), U1.53 (GPIO42/ADC2)
SRAM_A11: U2.23 (A11), U3.10 (IO6)
SRAM_A12: U2.2 (A12), U3.12 (IO7)
SRAM_A13: U2.26 (A13), U3.13 (IO8)
SRAM_A14: U2.1 (A14), U3.15 (IO9)
SRAM_CS: U2.20 (~CS), U3.18 (IO12)
SRAM_WE: U2.27 (~WE), U3.16 (IO10)
SWCLK: J7.5, U1.33 (SWCLK)
SWDIO: J7.6, U1.34 (SWDIO)
TRIG_RD: TP1.1 (1_1), U1.38 (GPIO30), U9.10 (IO6)
TRIG_WR: U1.39 (GPIO31), U9.12 (IO7)
USB_DM: J2.A6 (D+), J2.B7 (D-), U1.66 (USB_DM)
USB_DP: J2.A7 (D-), J2.B6 (D+), U1.67 (USB_DP)
VBUS: D1.2 (A), D2.2 (A), J2.A4 (VBUS), J2.A9 (VBUS), J2.B4 (VBUS), J2.B9 (VBUS)
VCC: D1.1 (K), FLG1.1, J3.1, U4.3 (EN), U9.1 (V_{DD}), U9.14 (V_{DD2})
VGG: C1.2, D2.1 (K), FLG2.1, J3.20, J5.4, U2.28 (VCC), U3.1 (V_{DD}), U3.14 (V_{DD2}), U4.1 (VIN), U10.7 (VCCB)
VREG_LX: L2.2, U1.63 (VREG_LX)
XIN: C12.2, U1.30 (XIN), X1.1
XOUT: C13.2, R11.2, X1.3
XOUT_MCU: R11.1, U1.31 (XOUT)
Y0: J3.4
Y2: J3.19
